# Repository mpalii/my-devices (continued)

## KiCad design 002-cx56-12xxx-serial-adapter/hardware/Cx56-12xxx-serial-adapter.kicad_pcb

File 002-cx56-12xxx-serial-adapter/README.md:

# 002-cx56-12xxx-serial-adapter
SN64HC595 based serial adapter for Cx54-21xxx displays

Simulation:

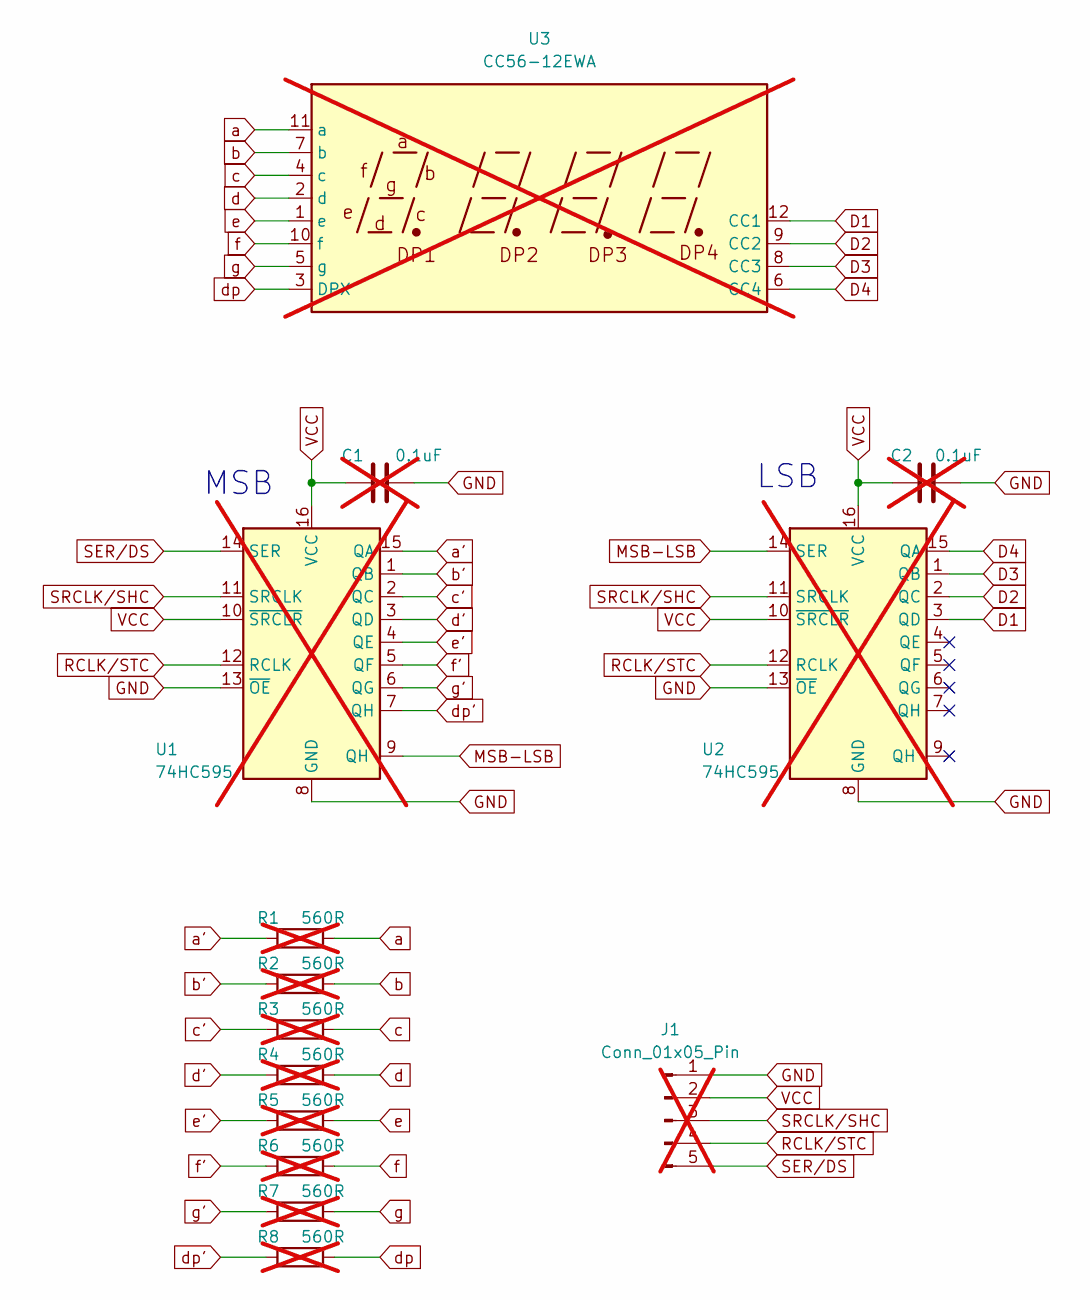
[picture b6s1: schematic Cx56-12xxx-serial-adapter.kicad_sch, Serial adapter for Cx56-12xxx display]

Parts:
C1, C2: 0.1uF; C_0805_2012Metric_Pad1.18x1.45mm_HandSolder; not fitted
J1: Conn_01x05_Pin; PinHeader_1x05_P2.54mm_Horizontal; not fitted
R1, R2, R3, R4, R5, R6, R7, R8: 560R; R_0805_2012Metric_Pad1.20x1.40mm_HandSolder; not fitted
U1, U2: 74HC595; SOP-16_3.9x9.9mm_P1.27mm; not fitted
U3: CC56-12EWA; CA56-12EWA; not fitted

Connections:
D1: U2.3 (QD), U3.12 (CC1)
D2: U2.2 (QC), U3.9 (CC2)
D3: U2.1 (QB), U3.8 (CC3)
D4: U2.15 (QA), U3.6 (CC4)
GND: C1.2, C2.2, J1.1, U1.8 (GND), U1.13 (~OE), U2.8 (GND), U2.13 (~OE)
MSB-LSB: U1.9 (QH'), U2.14 (SER)
RCLK/STC: J1.4, U1.12 (RCLK), U2.12 (RCLK)
SER/DS: J1.5, U1.14 (SER)
SRCLK/SHC: J1.3, U1.11 (SRCLK), U2.11 (SRCLK)
VCC: C1.1, C2.1, J1.2, U1.10 (~SRCLR), U1.16 (VCC), U2.10 (~SRCLR), U2.16 (VCC)
a: R1.1, U3.11 (a)
a': R1.2, U1.15 (QA)
b: R2.1, U3.7 (b)
b': R2.2, U1.1 (QB)
c: R3.1, U3.4 (c)
c': R3.2, U1.2 (QC)
d: R4.1, U3.2 (d)
d': R4.2, U1.3 (QD)
dp: R8.1, U3.3 (DPX)
dp': R8.2, U1.7 (QH)
e: R5.1, U3.1 (e)
e': R5.2, U1.4 (QE)
f: R6.1, U3.10 (f)
f': R6.2, U1.5 (QF)
g: R7.1, U3.5 (g)
g': R7.2, U1.6 (QG)

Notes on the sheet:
MSB
LSB

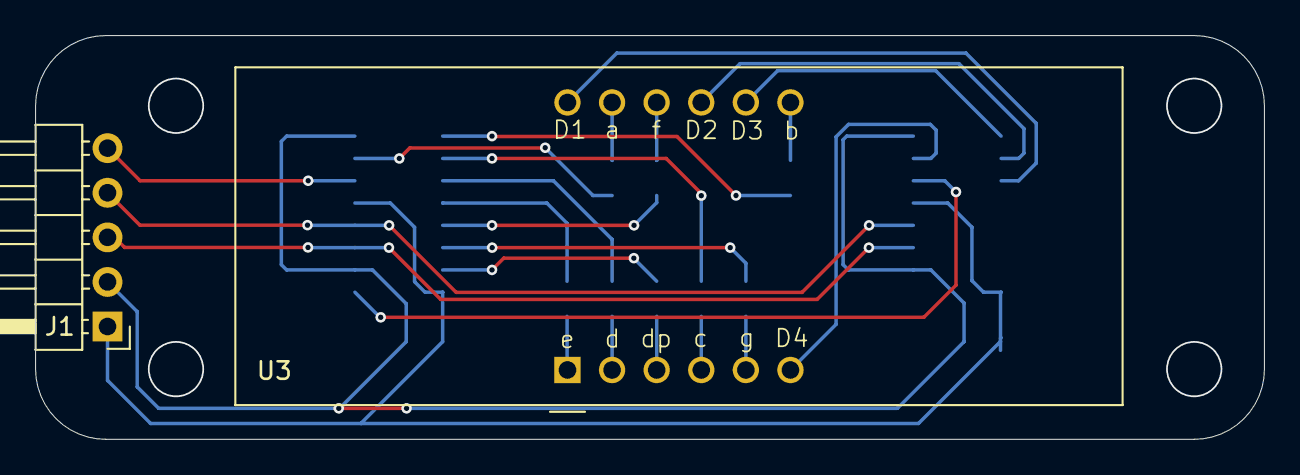
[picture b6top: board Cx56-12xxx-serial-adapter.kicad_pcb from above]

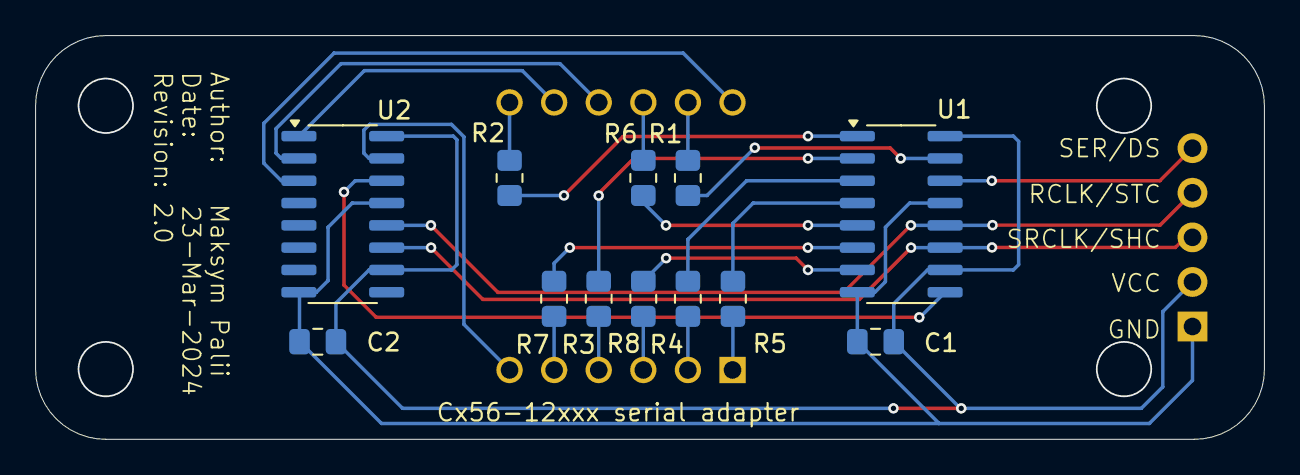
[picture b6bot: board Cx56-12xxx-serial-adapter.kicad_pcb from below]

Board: 2 copper layers, 70.0 x 23.0 mm, 14 parts (12 on the bottom side), 26 nets.

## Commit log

2024-04-06 License adding
2024-04-06 Example of VScode properties
2024-04-06 Adding the .gitignore file
2024-04-06 001: reaction time tester (migration from separate repository)
2024-04-06 002: serial adapter for cx46-12xxx compatible seven-segment dispalys
2024-04-20 003: tic-tac-toe - PVP mode
2024-04-21 003: tic-tac-toe - evaluation and PVP mode
2024-04-26 002: serial adapter for cx46-12xxx refactoring
2024-10-06 004: ATmega644 evaluation board
2024-11-20 001: high precision reaction time measuring
2024-11-27 001: pins reassignement
2024-11-29 001: hardware refactoring
2024-11-29 001: simulation refactoring (with Proteus)
2024-11-29 001: pin assignment fix
2024-11-30 001: removed old implementation
2024-11-30 001: README.md adjustment
2024-12-15 001: reduce measurement delay, pull-up uart RX line
2025-01-05 003: hardware
2025-06-08 005: init project
2025-07-01 005: IR sensors polling, serial communication
2025-07-07 005: PCB and simple firmware
